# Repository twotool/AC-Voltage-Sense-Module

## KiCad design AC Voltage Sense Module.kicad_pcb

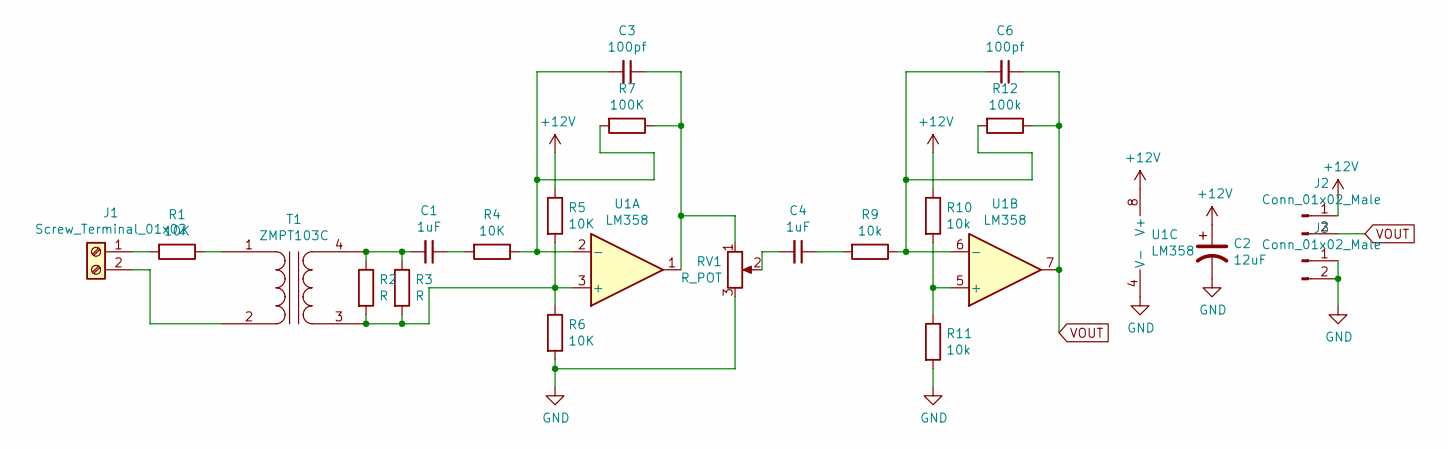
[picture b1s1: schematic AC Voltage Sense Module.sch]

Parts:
C1, C4: 1uF; C_Disc_D6.0mm_W2.5mm_P5.00mm
C2: 12uF; CP_Radial_D6.3mm_P2.50mm
C3, C6: 100pf; C_Disc_D6.0mm_W2.5mm_P5.00mm
J1: Screw_Terminal_01x02; TerminalBlock_Phoenix_MKDS-1,5-2-5.08_1x02_P5.08mm_Horizont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
J2, J3: Conn_01x02_Male; PinHeader_1x02_P2.54mm_Vertical
R1, R4, R5, R6: 10K; R_Axial_DIN0309_L9.0mm_D3.2mm_P12.70mm_Horizontal
R2, R3: R; R_Axial_DIN0309_L9.0mm_D3.2mm_P12.70mm_Horizontal
R7: 100K; R_Axial_DIN0309_L9.0mm_D3.2mm_P12.70mm_Horizontal
R9, R10, R11: 10k; R_Axial_DIN0309_L9.0mm_D3.2mm_P12.70mm_Horizontal
R12: 100k; R_Axial_DIN0309_L9.0mm_D3.2mm_P12.70mm_Horizontal
RV1: R_POT; Potentiometer_Bourns_3296W_Vertical
T1: ZMPT103C; ZMPT101B
U1: LM358; DIP-8_W10.16mm_LongPads

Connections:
+12V: C2.1, J2.1, R5.1, R10.1, U1.8 (V+); also elsewhere on the board
GND: C2.2, J3.1, J3.2, R6.2, R11.2, RV1.3, U1.4 (V-); also elsewhere on the board
unnamed: C1.1, R4.2
unnamed: C1.2, R2.1, R3.1, T1.4 (SB)
unnamed: C3.1, R7.1, RV1.1, U1.1
unnamed: C3.2, R4.1, R7.2, U1.2 (-)
unnamed: C4.1, R9.2
unnamed: C4.2, RV1.2
unnamed: C6.2, R9.1, R12.2, U1.6 (-)
unnamed: J1.1, R1.2
unnamed: J1.2, T1.2 (PB)
unnamed: R1.1, T1.1 (PA)
unnamed: R2.2, R3.2, R5.2, R6.1, T1.3 (SA), U1.3 (+)
unnamed: R10.2, R11.1, U1.5 (+)
VOUT: C6.1, J2.2, R12.1, U1.7; also elsewhere on the board

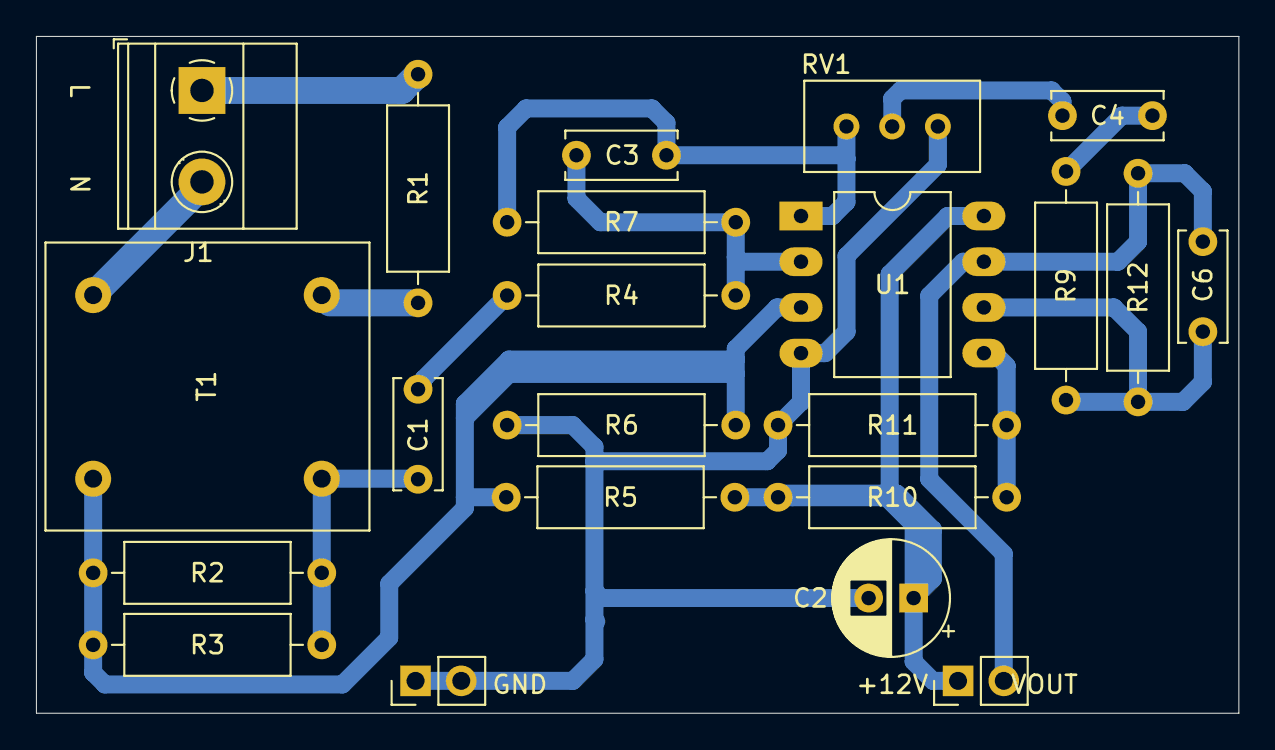
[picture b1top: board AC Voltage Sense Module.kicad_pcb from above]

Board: 2 copper layers, 66.8 x 37.6 mm, 22 parts (0 on the bottom side), 15 nets.

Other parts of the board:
+12V: Conn_01x02_Male; PinHeader_1x02_P2.54mm_Vertical
GND: Conn_01x02_Male; PinHeader_1x02_P2.54mm_Vertical

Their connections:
+12V: +12V.1; also elsewhere on the board
GND: GND.1, GND.2; also elsewhere on the board
VOUT: +12V.2; also elsewhere on the board
